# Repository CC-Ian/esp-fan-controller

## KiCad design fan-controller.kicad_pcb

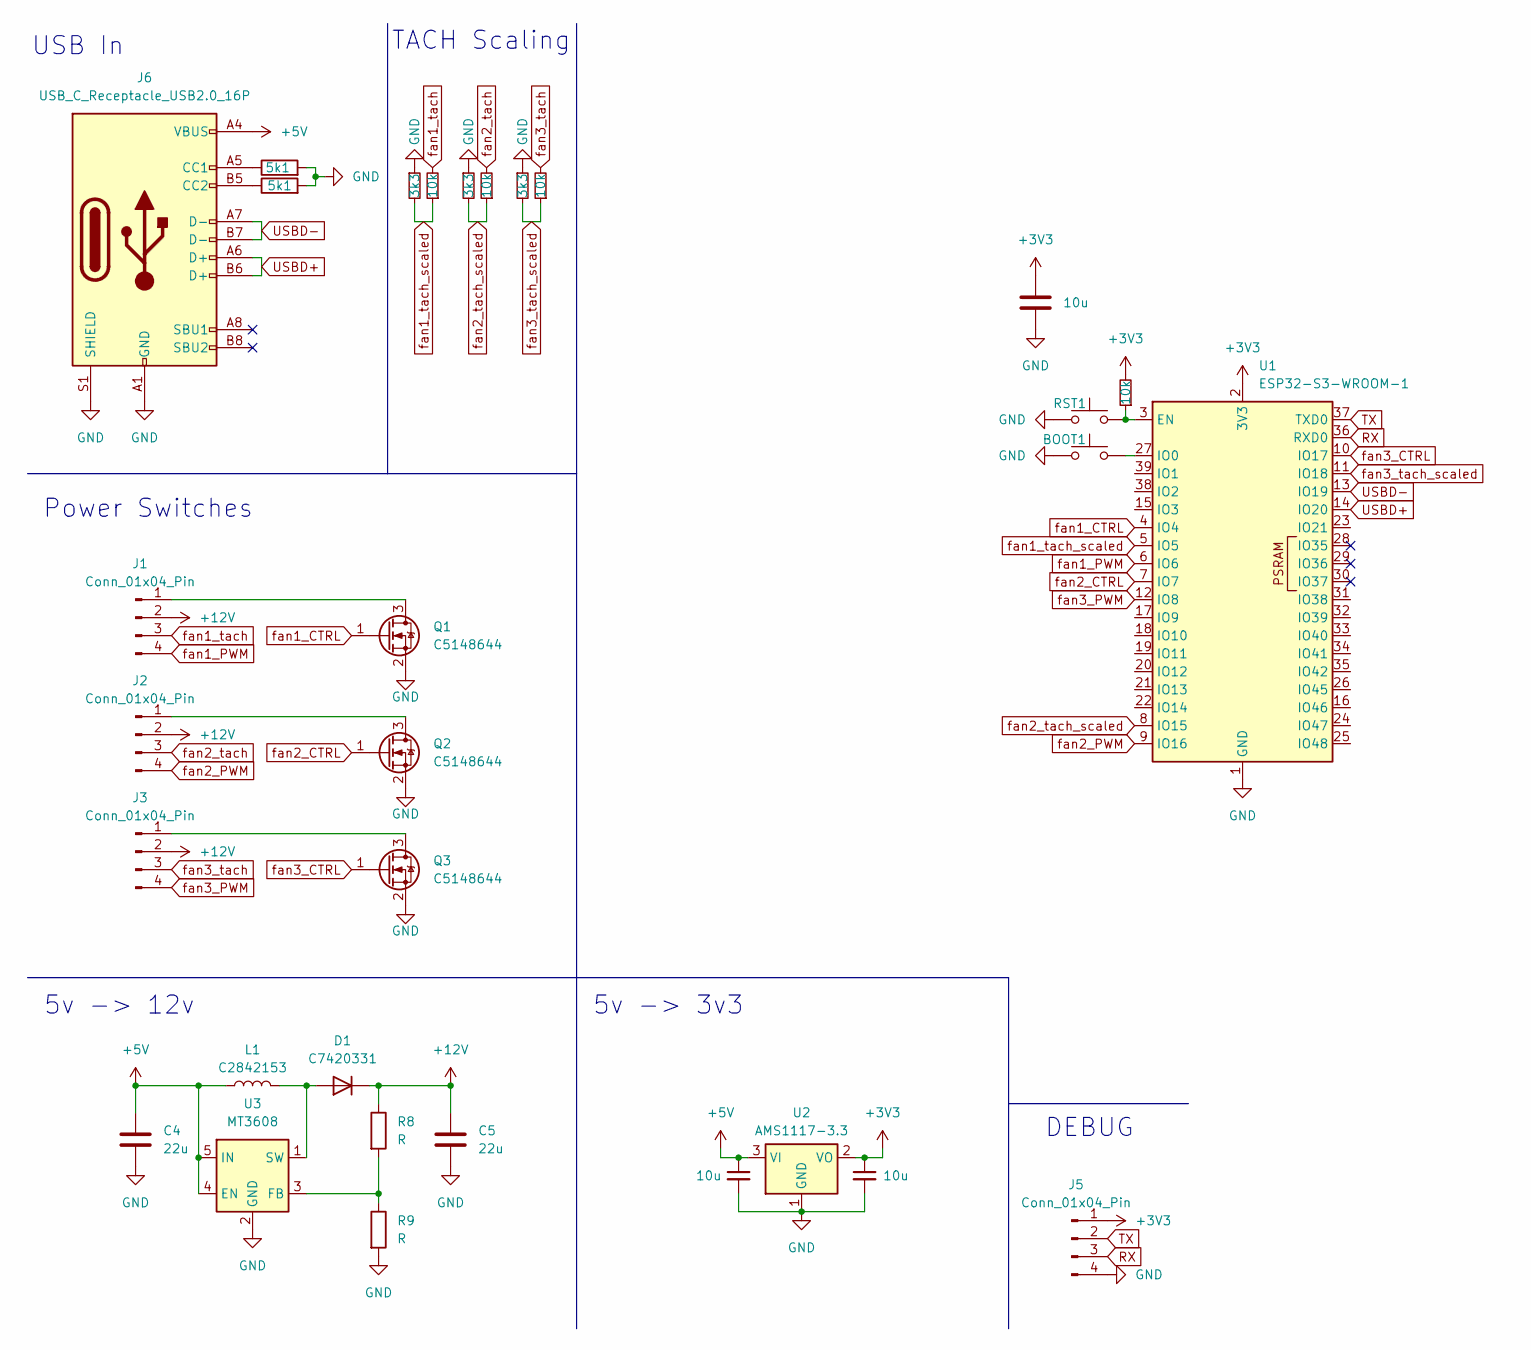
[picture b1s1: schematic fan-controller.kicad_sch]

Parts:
BOOT1: SW_Push; SW_SPST_SKQG_WithStem
C1, C2, C3: 10u; C_0603_1608Metric
C4, C5: 22u; C_0805_2012Metric
D1: C7420331; D_SOD-323
J1, J2, J3: Conn_01x04_Pin; FanPinHeader_1x04_P2.54mm_Vertical
J5: Conn_01x04_Pin; PinHeader_1x04_P2.54mm_Vertical
J6: USB_C_Receptacle_USB2.0_16P; USB_C_Receptacle_HRO_TYPE-C-31-M-12
L1: C2842153; L_Chilisin_BMRB00050518-B
Q1, Q2, Q3: C5148644; SOT-523
R1: 10k; R_0603_1608Metric
R2, R4, R6: 10k; R_0402_1005Metric
R3, R5, R7: 3k3; R_0402_1005Metric
R8, R9: R; R_0402_1005Metric
R10, R11: 5k1; R_0402_1005Metric
RST1: SW_Push; SW_SPST_SKQG_WithStem
U1: ESP32-S3-WROOM-1
U2: AMS1117-3.3; SOT-223-3_TabPin2
U3: MT3608; SOT-23-6

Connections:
+3V3: C2.1, C3.1, J5.1, R1.2, U1.2 (3V3), U2.2 (VO)
+5V: C1.1, C4.1, J6.A4 (VBUS), J6.A9 (VBUS), J6.B4 (VBUS), J6.B9 (VBUS), L1.1, U2.3 (VI), U3.4 (EN), U3.5 (IN)
+12V: C5.1, D1.1 (K), J1.2, J2.2, J3.2, R8.1
GND: BOOT1.1, C1.2, C2.2, C3.2, C4.2, C5.2, J5.4, J6.A1 (GND), J6.A12 (GND), J6.B1 (GND), J6.B12 (GND), J6.S1 (SHIELD), Q1.2 (S), Q2.2 (S), Q3.2 (S), R3.1, R5.1, R7.1, R9.2, R10.2, R11.2, RST1.1, U1.1 (GND), U1.40 (GND), U1.41 (GND), U2.1 (GND), U3.2 (GND)
unnamed: D1.2 (A), L1.2, U3.1 (SW)
unnamed: J1.1, Q1.3 (D)
unnamed: J2.1, Q2.3 (D)
unnamed: J3.1, Q3.3 (D)
unnamed: J6.A5 (CC1), R10.1
unnamed: J6.B5 (CC2), R11.1
unnamed: R1.1, RST1.2, U1.3 (EN)
unnamed: BOOT1.2, U1.27 (IO0)
unnamed: R8.2, R9.1, U3.3 (FB)
RX: J5.3, U1.36 (RXD0)
TX: J5.2, U1.37 (TXD0)
USBD+: J6.A6 (D+), J6.B6 (D+), U1.14 (IO20)
USBD-: J6.A7 (D-), J6.B7 (D-), U1.13 (IO19)
fan1_CTRL: Q1.1 (G), U1.4 (IO4)
fan1_PWM: J1.4, U1.6 (IO6)
fan1_tach: J1.3, R4.2
fan1_tach_scaled: R4.1, R5.2, U1.5 (IO5)
fan2_CTRL: Q2.1 (G), U1.7 (IO7)
fan2_PWM: J2.4, U1.9 (IO16)
fan2_tach: J2.3, R2.2
fan2_tach_scaled: R2.1, R3.2, U1.8 (IO15)
fan3_CTRL: Q3.1 (G), U1.10 (IO17)
fan3_PWM: J3.4, U1.12 (IO8)
fan3_tach: J3.3, R6.2
fan3_tach_scaled: R6.1, R7.2, U1.11 (IO18)

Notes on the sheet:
TACH Scaling
USB In
5v -> 3v3
Power Switches
5v -> 12v
DEBUG

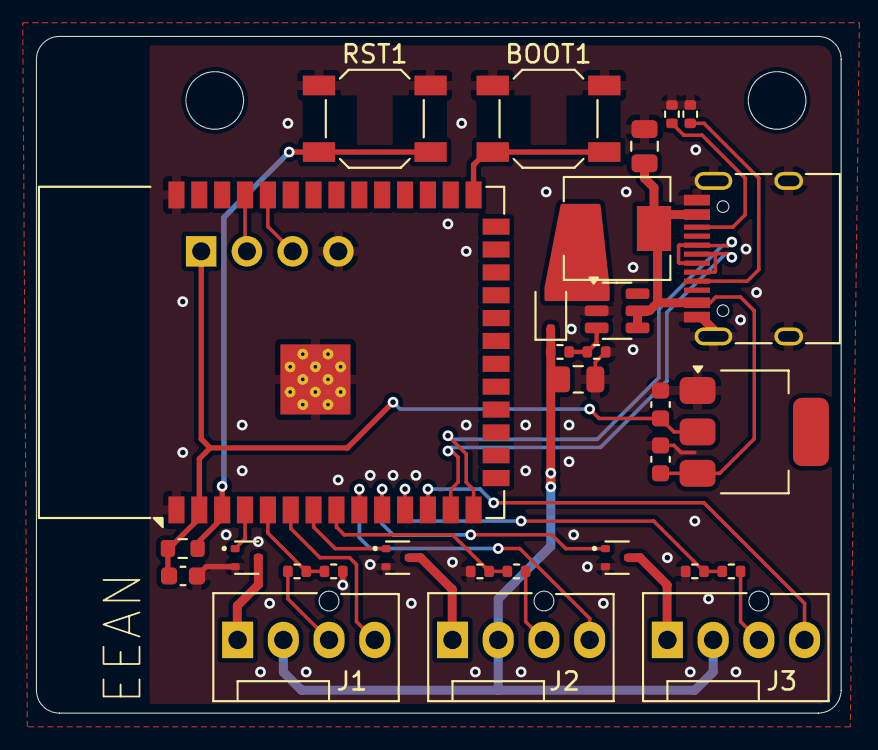
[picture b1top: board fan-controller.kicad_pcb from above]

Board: 2 copper layers, 44.7 x 37.6 mm, 31 parts (1 on the bottom side), 29 nets.

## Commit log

2024-08-02 add board
2024-08-05 Add gitignore
2024-08-05 Add backup files, Final layout
2024-08-05 Remove spares. Settle on final design
